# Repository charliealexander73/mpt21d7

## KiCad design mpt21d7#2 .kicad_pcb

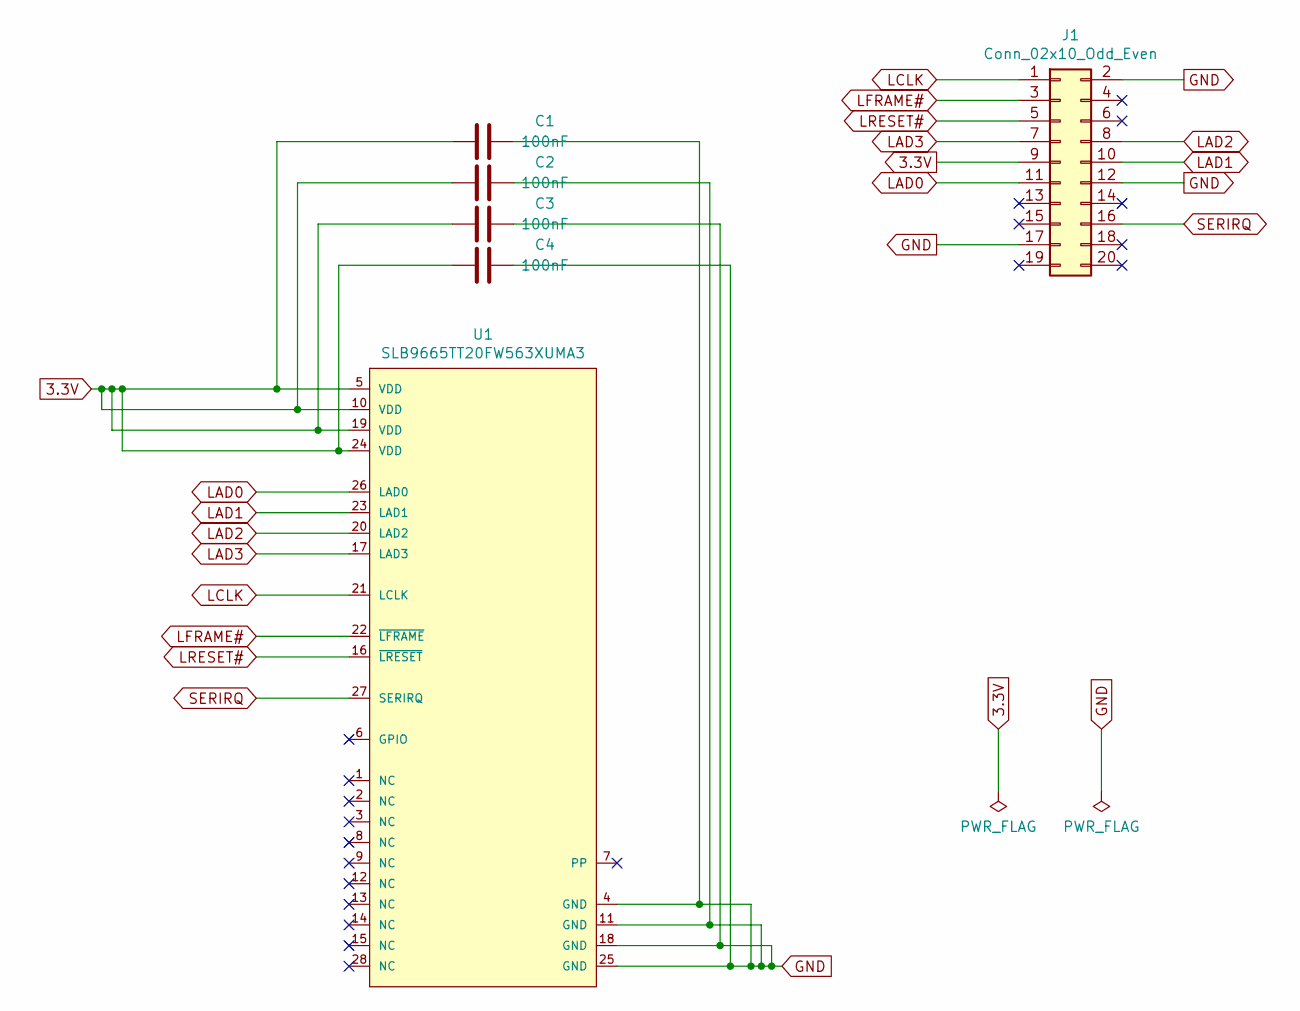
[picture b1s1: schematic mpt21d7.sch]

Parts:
C1, C2, C3, C4: 100nF; C_0603_1608Metric_Pad1.08x0.95mm_HandSolder
J1: Conn_02x10_Odd_Even; PinSocket_2x10_P2.54mm_Horizontal
U1: SLB9665TT20FW563XUMA3; Infineon-PG-TSSOP-28-0-2-IPC_C; mouser part number 726-SLB9665T20F563A3; digikey description TPM

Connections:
3.3V: C1.2, C2.2, C3.2, C4.2, J1.9, U1.5 (VDD), U1.10 (VDD), U1.19 (VDD), U1.24 (VDD)
GND: C1.1, C2.1, C3.1, C4.1, J1.2, J1.12, J1.17, U1.4 (GND), U1.11 (GND), U1.18 (GND), U1.25 (GND)
LAD0: J1.11, U1.26 (LAD0)
LAD1: J1.10, U1.23 (LAD1)
LAD2: J1.8, U1.20 (LAD2)
LAD3: J1.7, U1.17 (LAD3)
LCLK: J1.1, U1.21 (LCLK)
LFRAME#: J1.3, U1.22 (~LFRAME~)
LRESET#: J1.5, U1.16 (~LRESET~)
SERIRQ: J1.16, U1.27 (SERIRQ)

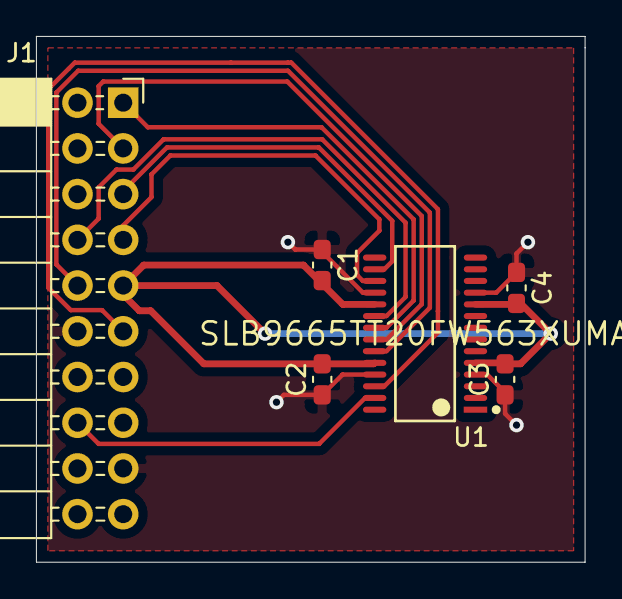
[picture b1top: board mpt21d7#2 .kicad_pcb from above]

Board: 2 copper layers, 30.5 x 29.2 mm, 6 parts (0 on the bottom side), 10 nets.
